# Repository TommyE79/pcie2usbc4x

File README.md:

# PCIe x4 to USB-C Adaptoid

A PCIe to USB-C adapter board -- plugs into a PCIe 4x card slot to breakout the data and clock lanes to a USB-C connector. 
Includes AC coupling caps and jumper resistors to aid in debugging/hacking.
Tested up to PCIe Gen 2 at 5.0 Gbps (though threre's plenty of room for improving the signal integrity).

[x] in 2nd step updating to PCIe 3.0 Standart

### Schematic

#### 
#### 
#### 

### PCB Bottom Side

#### 

### PCB Top Side

####

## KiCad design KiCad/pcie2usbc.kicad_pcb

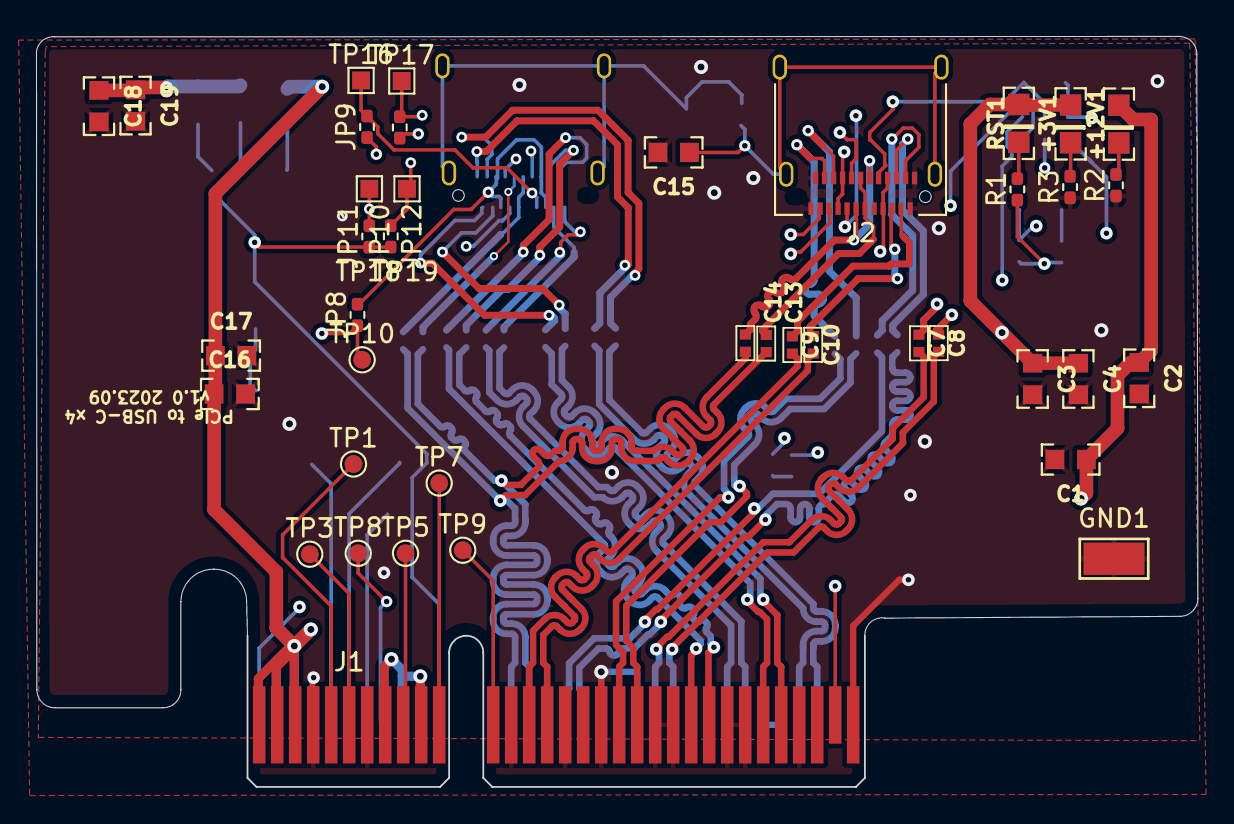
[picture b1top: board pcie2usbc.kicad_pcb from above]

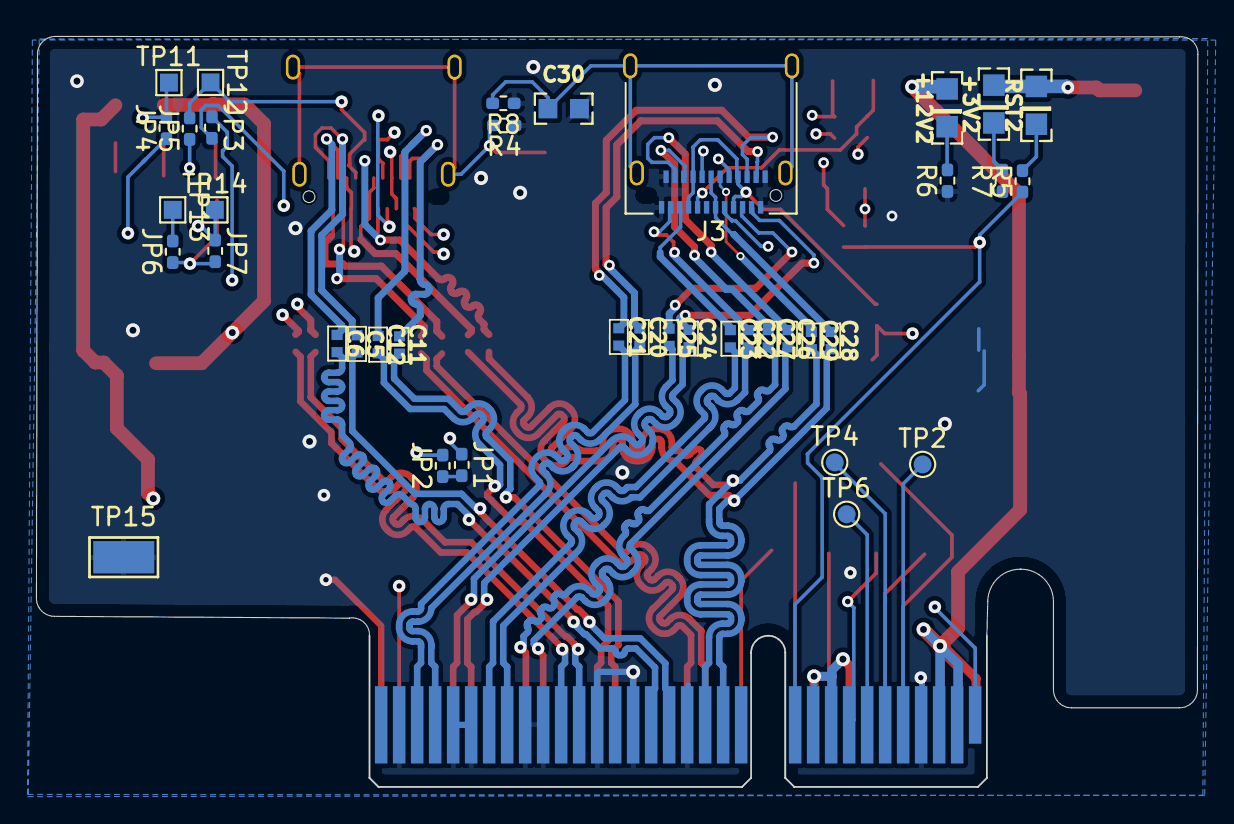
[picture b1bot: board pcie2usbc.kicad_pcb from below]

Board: 4 copper layers, 64.5 x 41.7 mm, 79 parts (39 on the bottom side), 72 nets.

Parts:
+3V1, +3V2, +12V1, +12V2: LEDSML0805; SML0805
C1, C3, C16, C18: 1u; C0603K
C2, C4, C15, C17, C19, C30: 100n; C0603K
C5, C6, C7, C8, C9, C10, C11, C12, C13, C14, C20, C21, C22, C23, C24, C25, C26, C27, C28, C29: 100n; C0402
GND1: TestPoint; TestPoint_Keystone_5015_Micro-Minature
J1: Bus_PCI_Express_x4; BUS_PCIexpress_x4
J2, J3: USB-C-MLX; USB_C_Receptacle_Amphenol_12401610E4-2A
JP1, JP2, JP3, JP4, JP5, JP6, JP7, JP8, JP9, JP10, JP11, JP12: 0; R_0402_1005Metric_Pad0.72x0.64mm_HandSolder
R1, R3, R5, R7: 2.2k; R_0402_1005Metric_Pad0.72x0.64mm_HandSolder
R2, R6: 10k; R_0402_1005Metric_Pad0.72x0.64mm_HandSolder
R4, R8: 100k; R_0402_1005Metric_Pad0.72x0.64mm_HandSolder
RST1, RST2: LEDSML0805; SML0805
TP1, TP2, TP3, TP4, TP5, TP6, TP7, TP8, TP9, TP10: TestPoint_Small; TestPoint_Pad_D1.0mm
TP11, TP12, TP13, TP14, TP16, TP17, TP18, TP19: TestPoint; TestPoint_Pad_1.0x1.0mm
TP15: TestPoint; TestPoint_Keystone_5015_Micro-Minature

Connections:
+3V3: +3V1.A, +3V2.A, C3.1, C4.1, C18.1, C19.1, J1.A9 (+3.3V), J1.A10 (+3.3V), J1.B8 (+3.3V), J1.B10 (3.3Vaux), RST1.A, RST2.A
+12V: +12V1.A, +12V2.A, C1.1, C2.1, C16.1, C17.1, J1.A2 (+12V), J1.A3 (+12V), J1.B1 (+12V), J1.B2 (+12V), J1.B3 (+12V)
/CLKREQ_N: J1.B12 (RSVD), TP9.1
/PER0_N: C6.2, J1.A17 (PERn0)
/PER0_P: C5.2, J1.A16 (PERp0)
/PER1_N: C8.2, J1.A22 (PERn1)
/PER1_P: C7.2, J1.A21 (PERp1)
/PER2_N: C23.2, J1.A26 (PERn2)
/PER2_P: C22.2, J1.A25 (PERp2)
/PER3_N: C21.2, J1.A30 (PERn3)
/PER3_P: C20.2, J1.A29 (PERp3)
/PERST_N: J1.A11 (~PERST), J2.A8 (SBU1), JP3.1, JP4.2, JP5.1, JP6.1, JP7.2, JP8.1, JP10.1, JP11.1, JP12.2, R1.1, R5.1, TP10.1, TP11.1
/PET0_N: C10.2, J1.B15 (PETn0)
/PET0_P: C9.2, J1.B14 (PETp0)
/PET1_N: C12.2, J1.B20 (PETn1)
/PET1_P: C11.2, J1.B19 (PETp1)
/PET2_N: C27.2, J1.B24 (PETn2)
/PET2_P: C26.2, J1.B23 (PETp2)
/PET3_N: C25.2, J1.B28 (PETn3)
/PET3_P: C24.2, J1.B27 (PETp3)
/PRSNT1: J1.A1 (~PRSNT1), JP1.1
/PRSNT2: J1.B31 (~PRSNT2), JP2.2
/PRSNT2_N: JP4.1, JP9.1
/PRSNT_SEL: JP1.2, JP2.1
/REFCLK_N: C14.2, C29.2, J1.A14 (REFCLK-)
/REFCLK_P: C13.2, C28.2, J1.A13 (REFCLK+)
/SMCLK: J1.B5 (SMCLK), TP1.1
/SMDAT: J1.B6 (SMDAT), TP3.1
/TCK: J1.A5 (JTAG2), TP2.1
/TDI: J1.A6 (JTAG3), TP4.1
/TDO: J1.A7 (JTAG4), TP6.1
/TMS: J1.A8 (JTAG5), TP8.1
/TRST_N: J1.B9 (JTAG1), TP5.1
/USB-C Lane1+2/CC1: J2.A5 (CC1), JP6.2, TP13.1
/USB-C Lane1+2/CC2: J2.B5 (CC2), JP7.1, TP14.1
/USB-C Lane1+2/D_N: C14.1, J2.A7 (DA-), J2.B7 (DB-)
/USB-C Lane1+2/D_P: C13.1, J2.A6 (DA+), J2.B6 (DB+)
/USB-C Lane1+2/RX1_N: C6.1, J2.B10 (RX1-)
/USB-C Lane1+2/RX1_P: C5.1, J2.B11 (RX1+)
/USB-C Lane1+2/RX2_N: C8.1, J2.A10 (RX2-)
/USB-C Lane1+2/RX2_P: C7.1, J2.A11 (RX2+)
/USB-C Lane1+2/SBU2: J2.B8 (SBU2), JP5.2, TP12.1
/USB-C Lane1+2/TX1_N: C10.1, J2.A3 (TX1-)
/USB-C Lane1+2/TX1_P: C9.1, J2.A2 (TX1+)
/USB-C Lane1+2/TX2_N: C12.1, J2.B3 (TX2-)
/USB-C Lane1+2/TX2_P: C11.1, J2.B2 (TX2+)
/USB-C Lane1+2/VBUS: J2.A4 (VBUS), J2.A9 (VBUS), J2.B4 (VBUS), J2.B9 (VBUS), JP3.2
/USB-C Lane3+4/CC1: J3.A5 (CC1), JP11.2, TP18.1
/USB-C Lane3+4/CC2: J3.B5 (CC2), JP12.1, TP19.1
/USB-C Lane3+4/D_N: C29.1, J3.A7 (DA-), J3.B7 (DB-)
/USB-C Lane3+4/D_P: C28.1, J3.A6 (DA+), J3.B6 (DB+)
/USB-C Lane3+4/RX1_N: C21.1, J3.B10 (RX1-)
/USB-C Lane3+4/RX1_P: C20.1, J3.B11 (RX1+)
/USB-C Lane3+4/RX2_N: C23.1, J3.A10 (RX2-)
/USB-C Lane3+4/RX2_P: C22.1, J3.A11 (RX2+)
/USB-C Lane3+4/SBU1: J3.A8 (SBU1), JP9.2, TP16.1
/USB-C Lane3+4/SBU2: J3.B8 (SBU2), JP10.2, TP17.1
/USB-C Lane3+4/TX1_N: C25.1, J3.A3 (TX1-)
/USB-C Lane3+4/TX1_P: C24.1, J3.A2 (TX1+)
/USB-C Lane3+4/TX2_N: C27.1, J3.B3 (TX2-)
/USB-C Lane3+4/TX2_P: C26.1, J3.B2 (TX2+)
/USB-C Lane3+4/VBUS: J3.A4 (VBUS), J3.A9 (VBUS), J3.B4 (VBUS), J3.B9 (VBUS), JP8.2
/WAKE_N: J1.B11 (~WAKE), TP7.1
GND: C1.2, C2.2, C3.2, C4.2, C15.2, C16.2, C17.2, C18.2, C19.2, C30.2, GND1.1, J1.A4 (GND), J1.A12 (GND), J1.A15 (GND), J1.A18 (GND), J1.A20 (GND), J1.A23 (GND), J1.A24 (GND), J1.A27 (GND), J1.A28 (GND), J1.A31 (GND), J1.B4 (GND), J1.B7 (GND), J1.B13 (GND), J1.B16 (GND), J1.B18 (GND), J1.B21 (GND), J1.B22 (GND), J1.B25 (GND), J1.B26 (GND), J1.B29 (GND), J1.B32 (GND), J2.A1 (GND), J2.A12 (GND), J2.B1 (GND), J2.B12 (GND), J3.A1 (GND), J3.A12 (GND), J3.B1 (GND), J3.B12 (GND), R2.1, R3.1, R4.1, R6.1, R7.1, R8.1, TP15.1
unnamed: +3V1.C, R3.2
unnamed: +3V2.C, R7.2
unnamed: +12V1.C, R2.2
unnamed: +12V2.C, R6.2
unnamed: C15.1, J2.S1 (SHIELD), R4.2
unnamed: C30.1, J3.S1 (SHIELD), R8.2
unnamed: R1.2, RST1.C
unnamed: R5.2, RST2.C

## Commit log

2023-08-24 Update README.md
    Update readme to branches
2023-08-24 Create LICENSE
    Create CERN open hardware licence
2023-09-06 WiP layout
2023-09-07 routing completed - review requested
2023-09-07 v1.0 final for reviwe
2023-09-07 Update issue templates
2023-09-08 reviwe - impedance matching
    as the impedance network settings didn't apply correctly, layout was redone with correct impedance
2023-09-15 Final rework
    Layout completed finally
2023-09-15 README.md update
    Layout completed finally
    updatede readme.md
